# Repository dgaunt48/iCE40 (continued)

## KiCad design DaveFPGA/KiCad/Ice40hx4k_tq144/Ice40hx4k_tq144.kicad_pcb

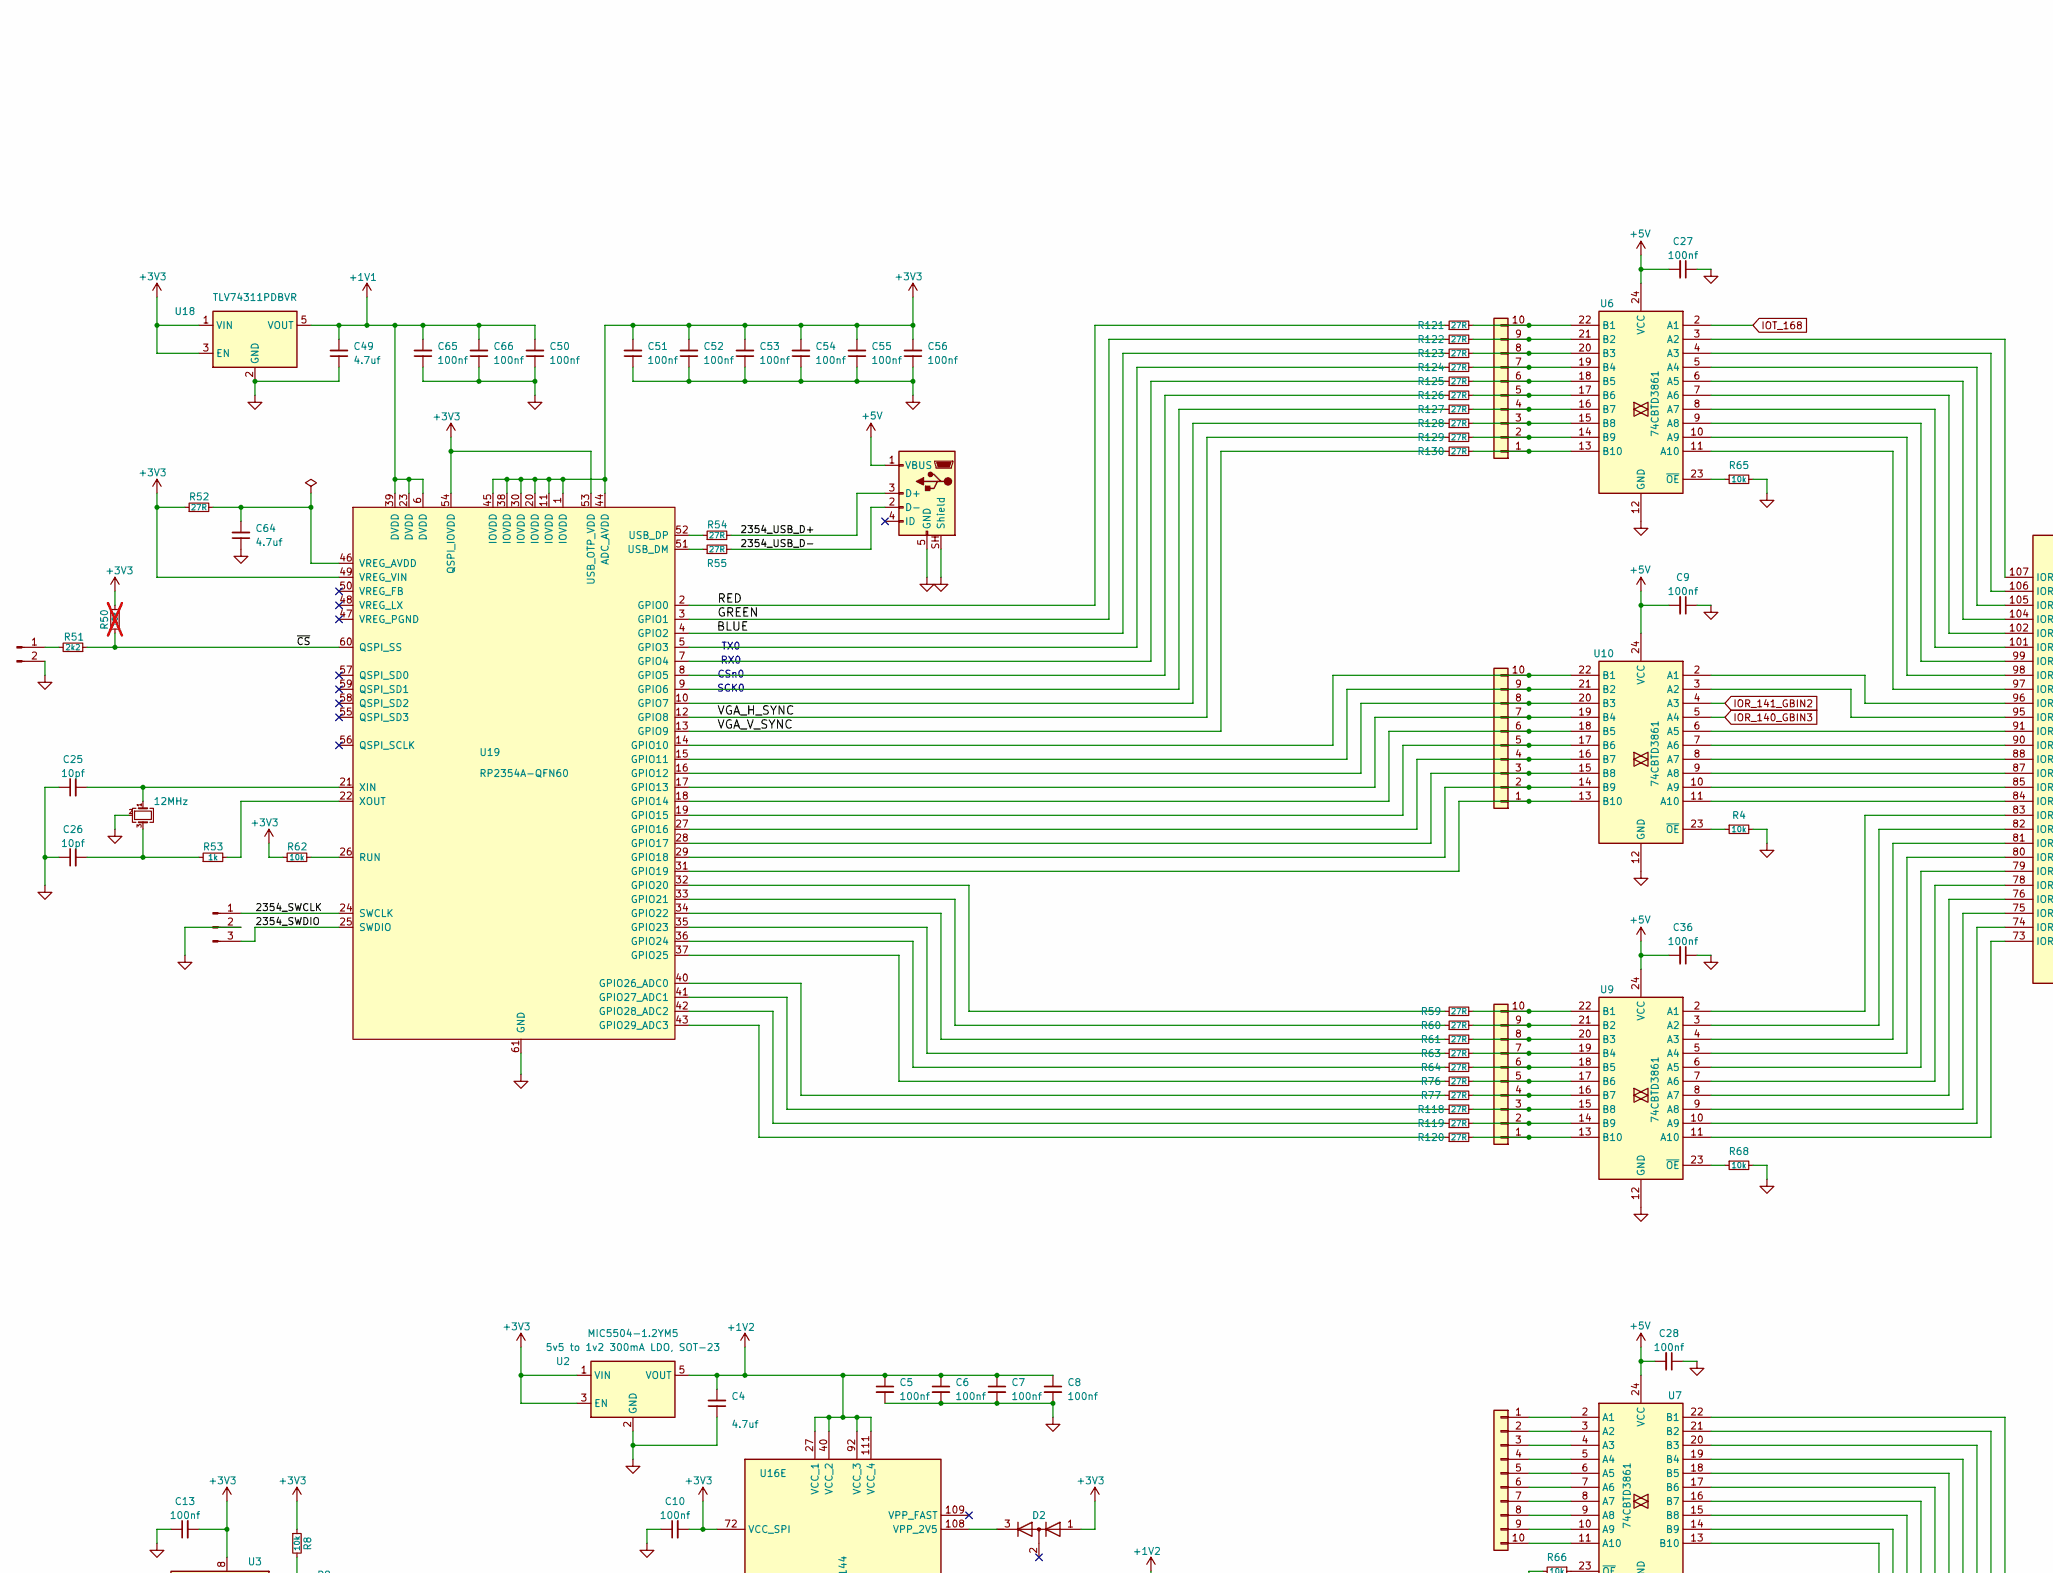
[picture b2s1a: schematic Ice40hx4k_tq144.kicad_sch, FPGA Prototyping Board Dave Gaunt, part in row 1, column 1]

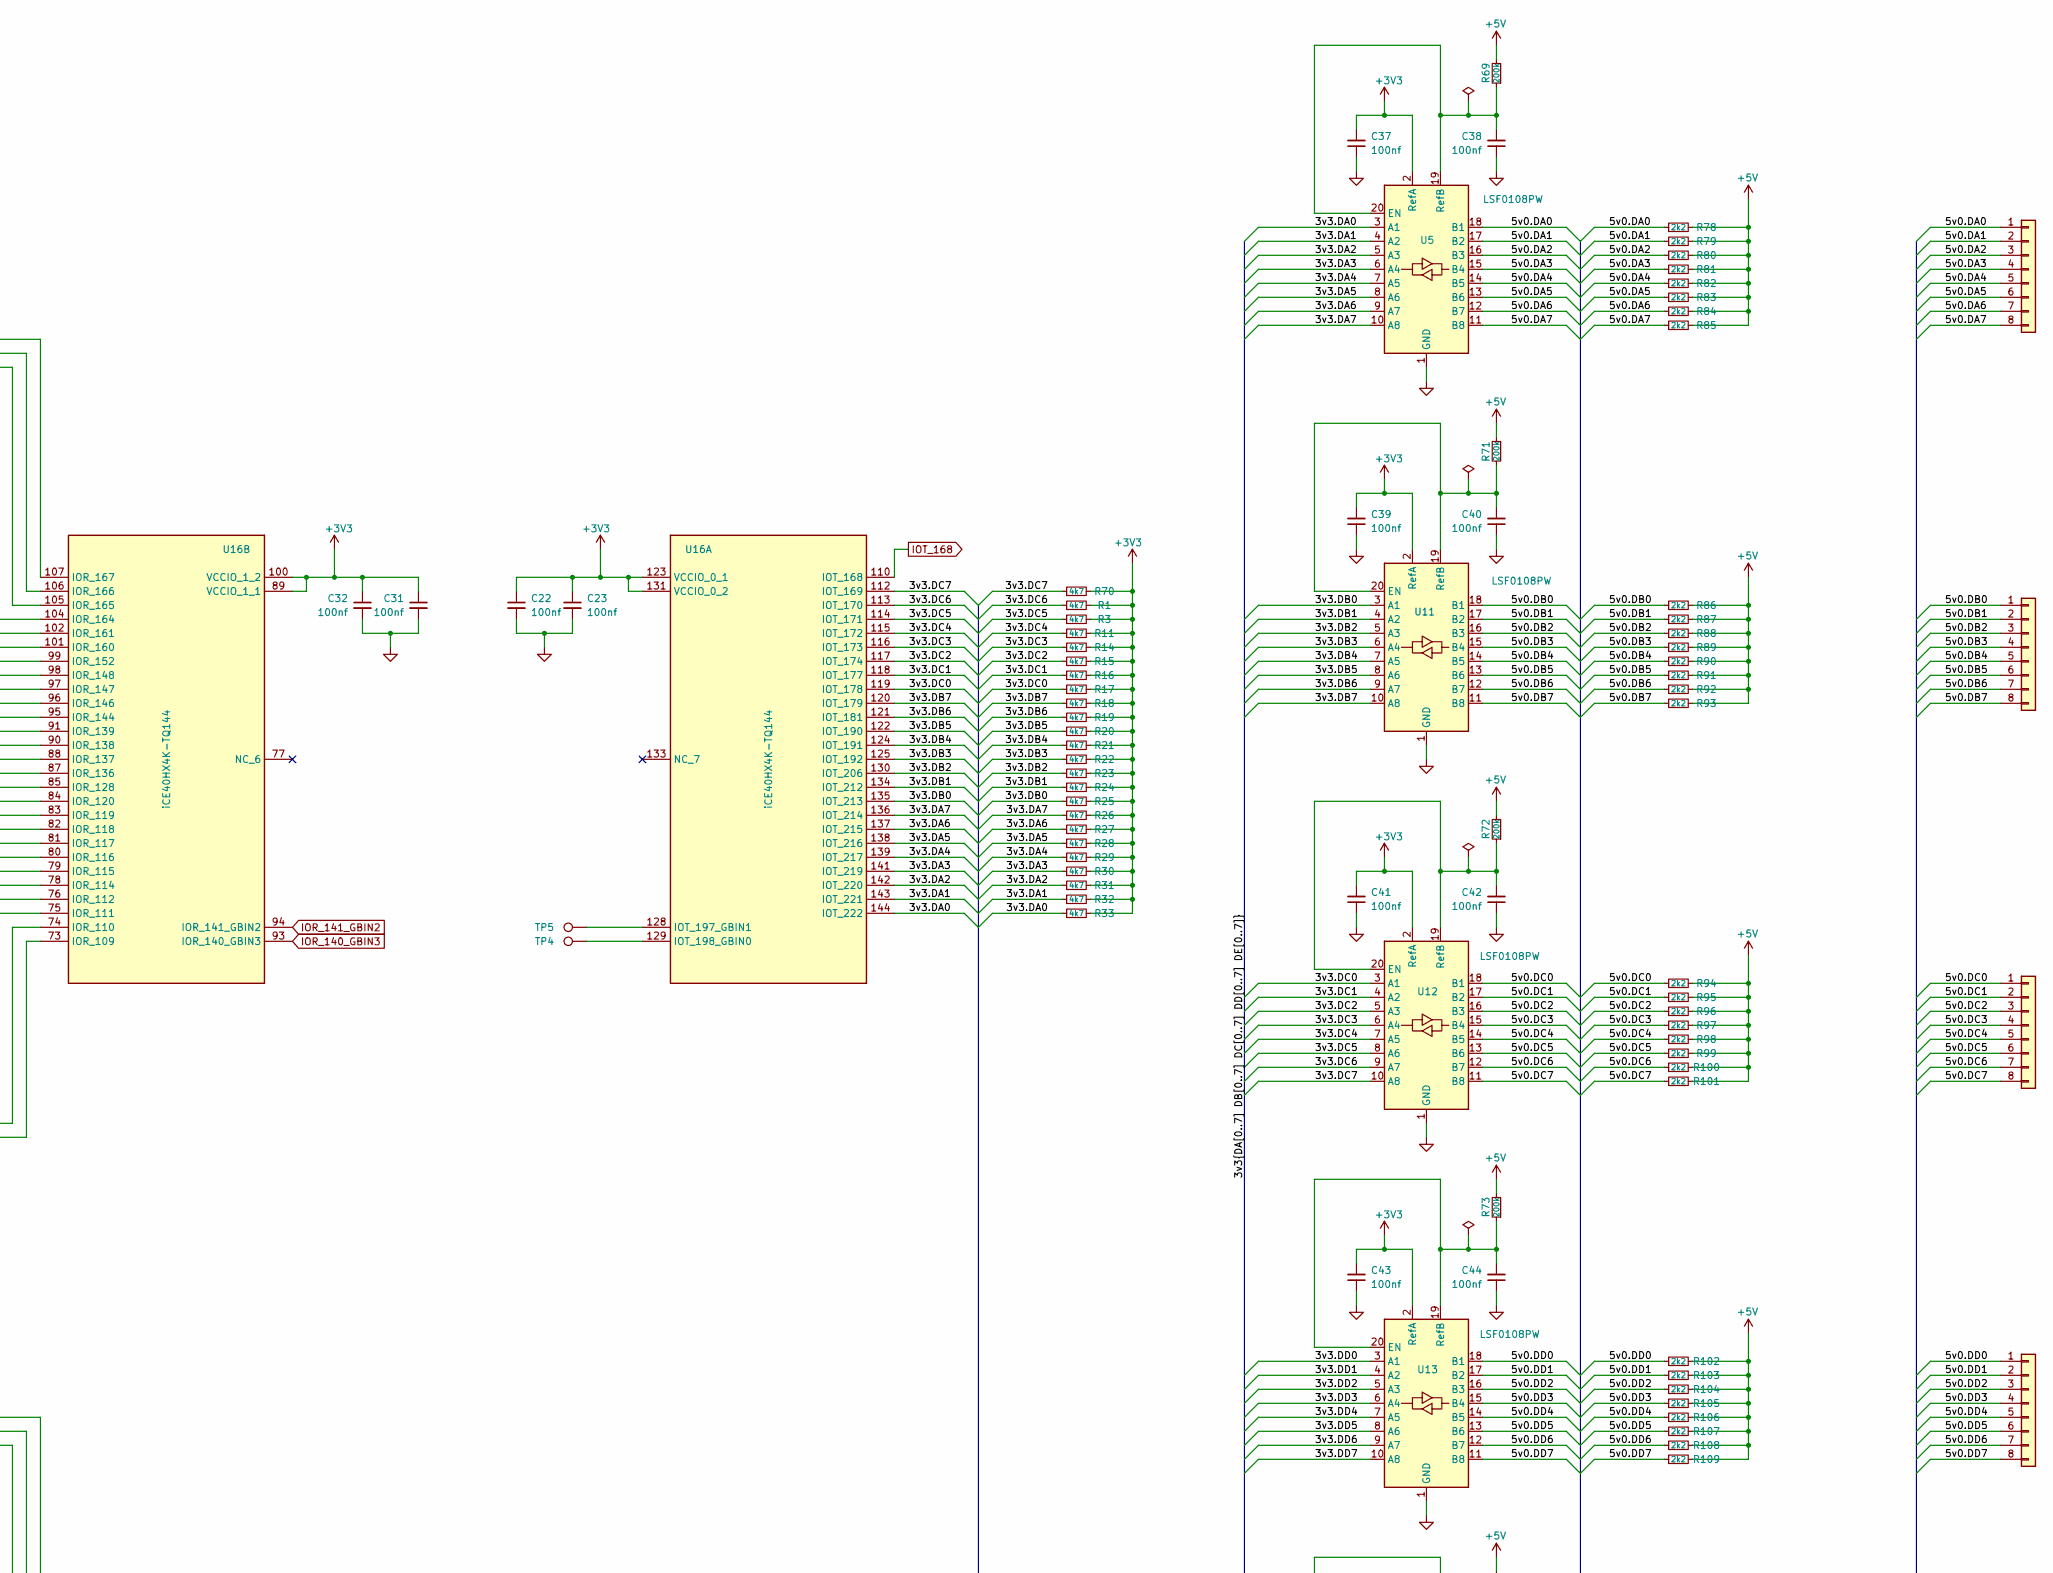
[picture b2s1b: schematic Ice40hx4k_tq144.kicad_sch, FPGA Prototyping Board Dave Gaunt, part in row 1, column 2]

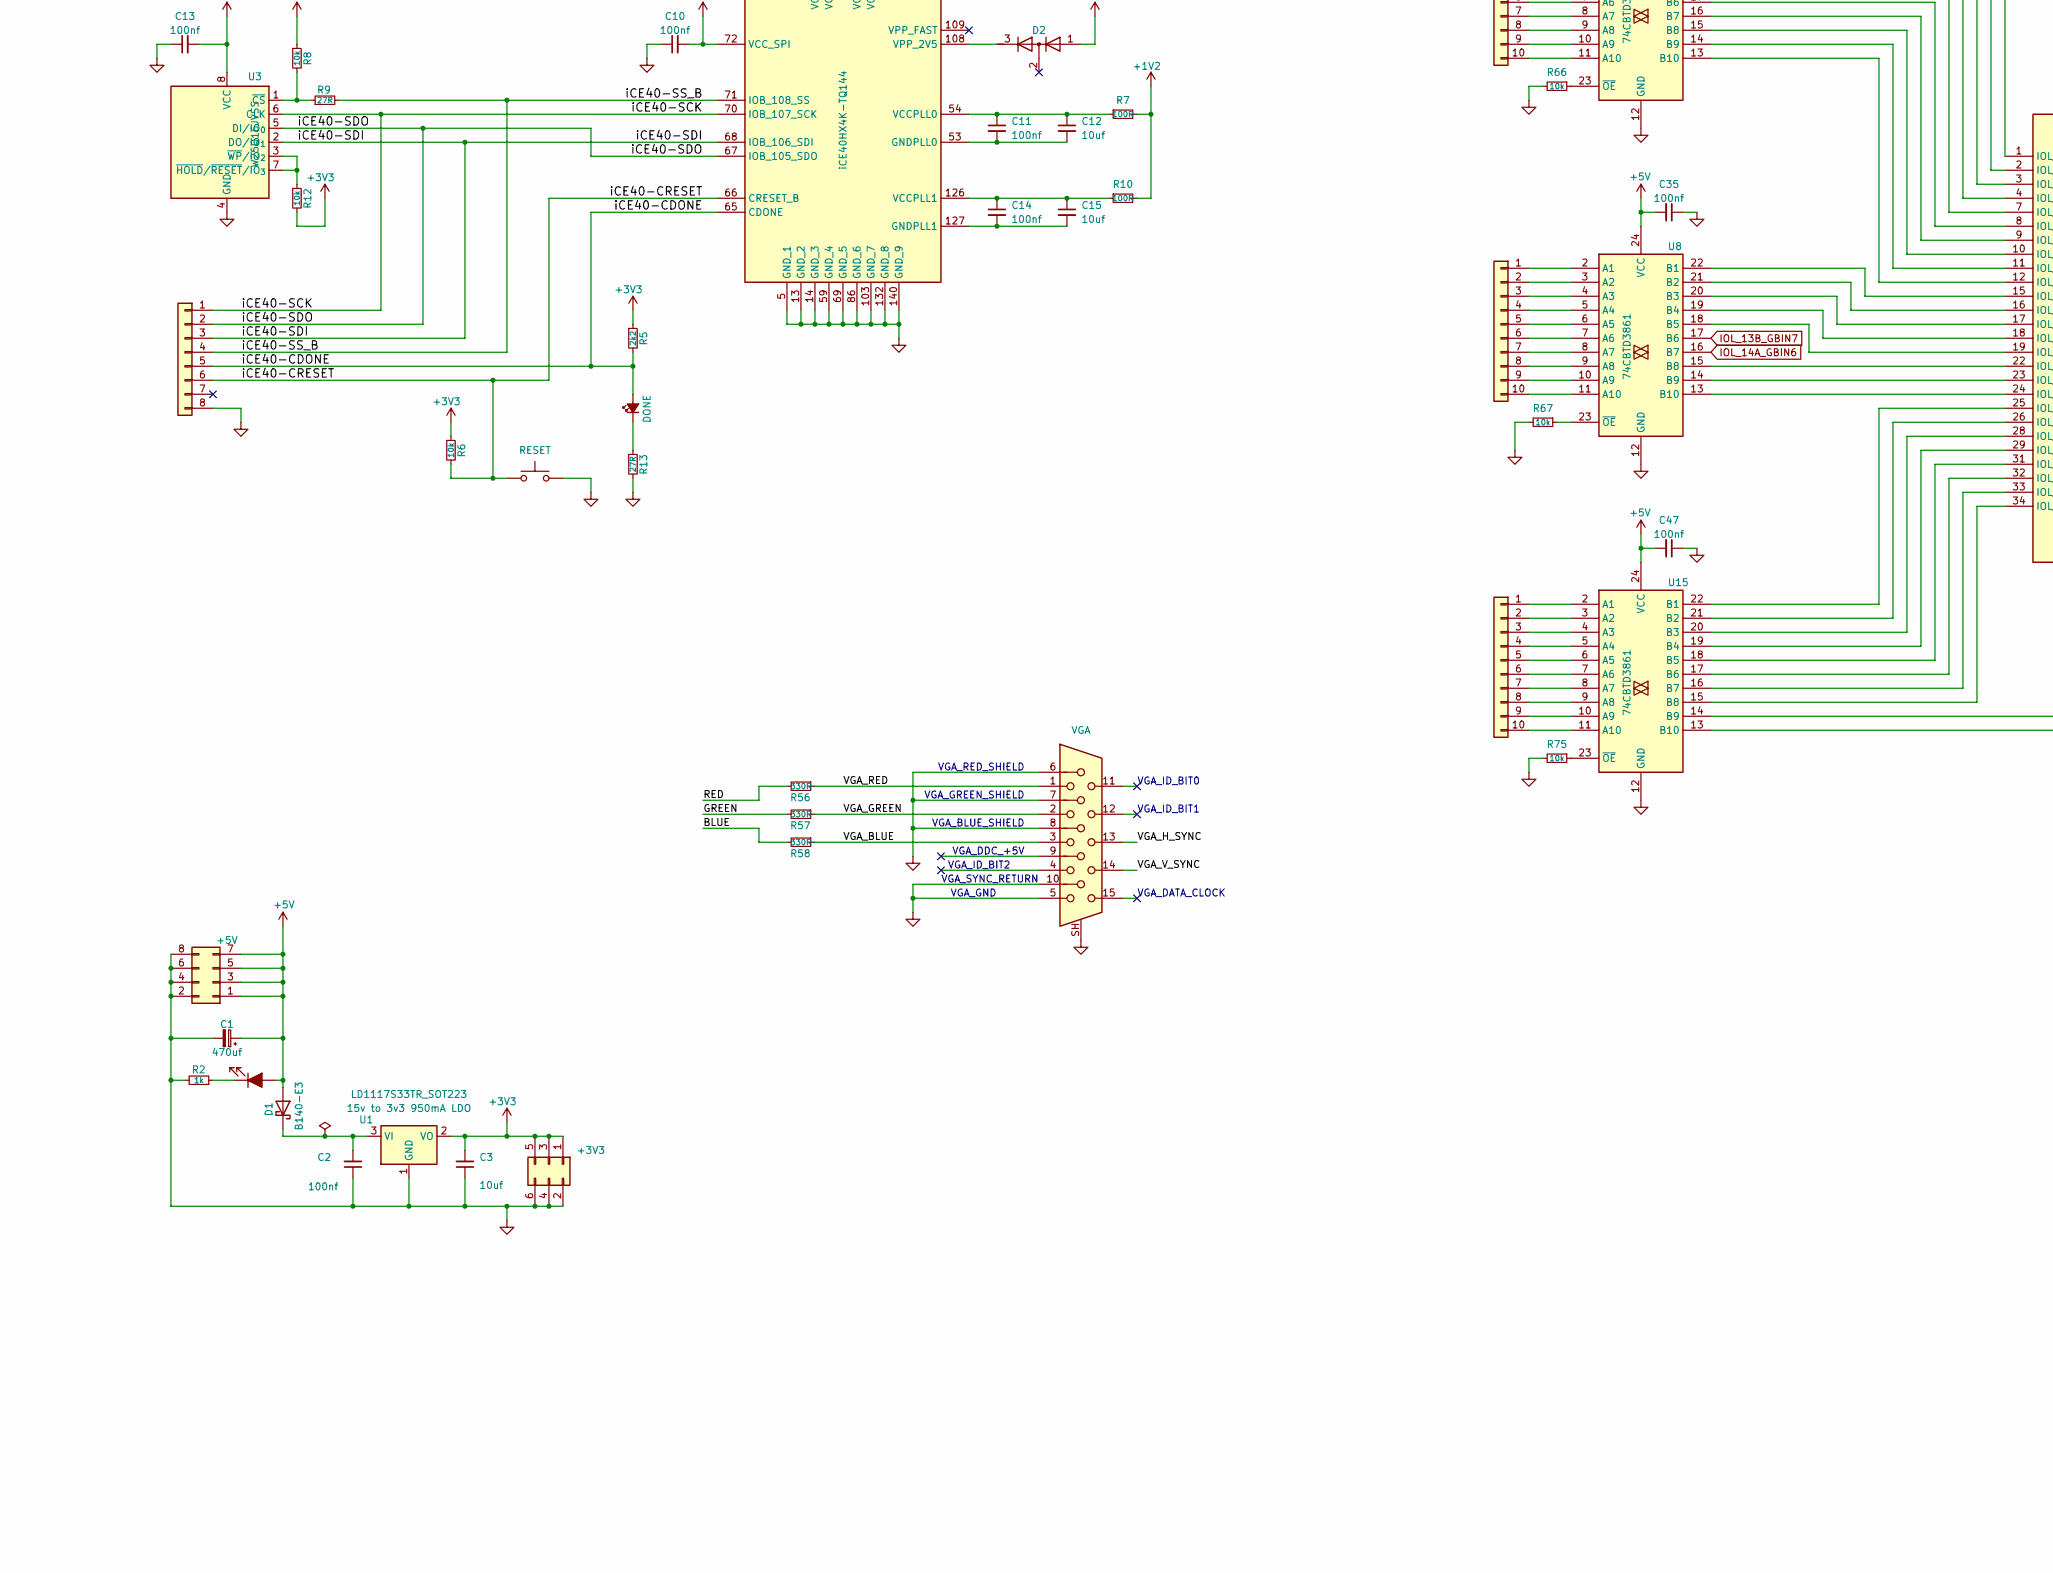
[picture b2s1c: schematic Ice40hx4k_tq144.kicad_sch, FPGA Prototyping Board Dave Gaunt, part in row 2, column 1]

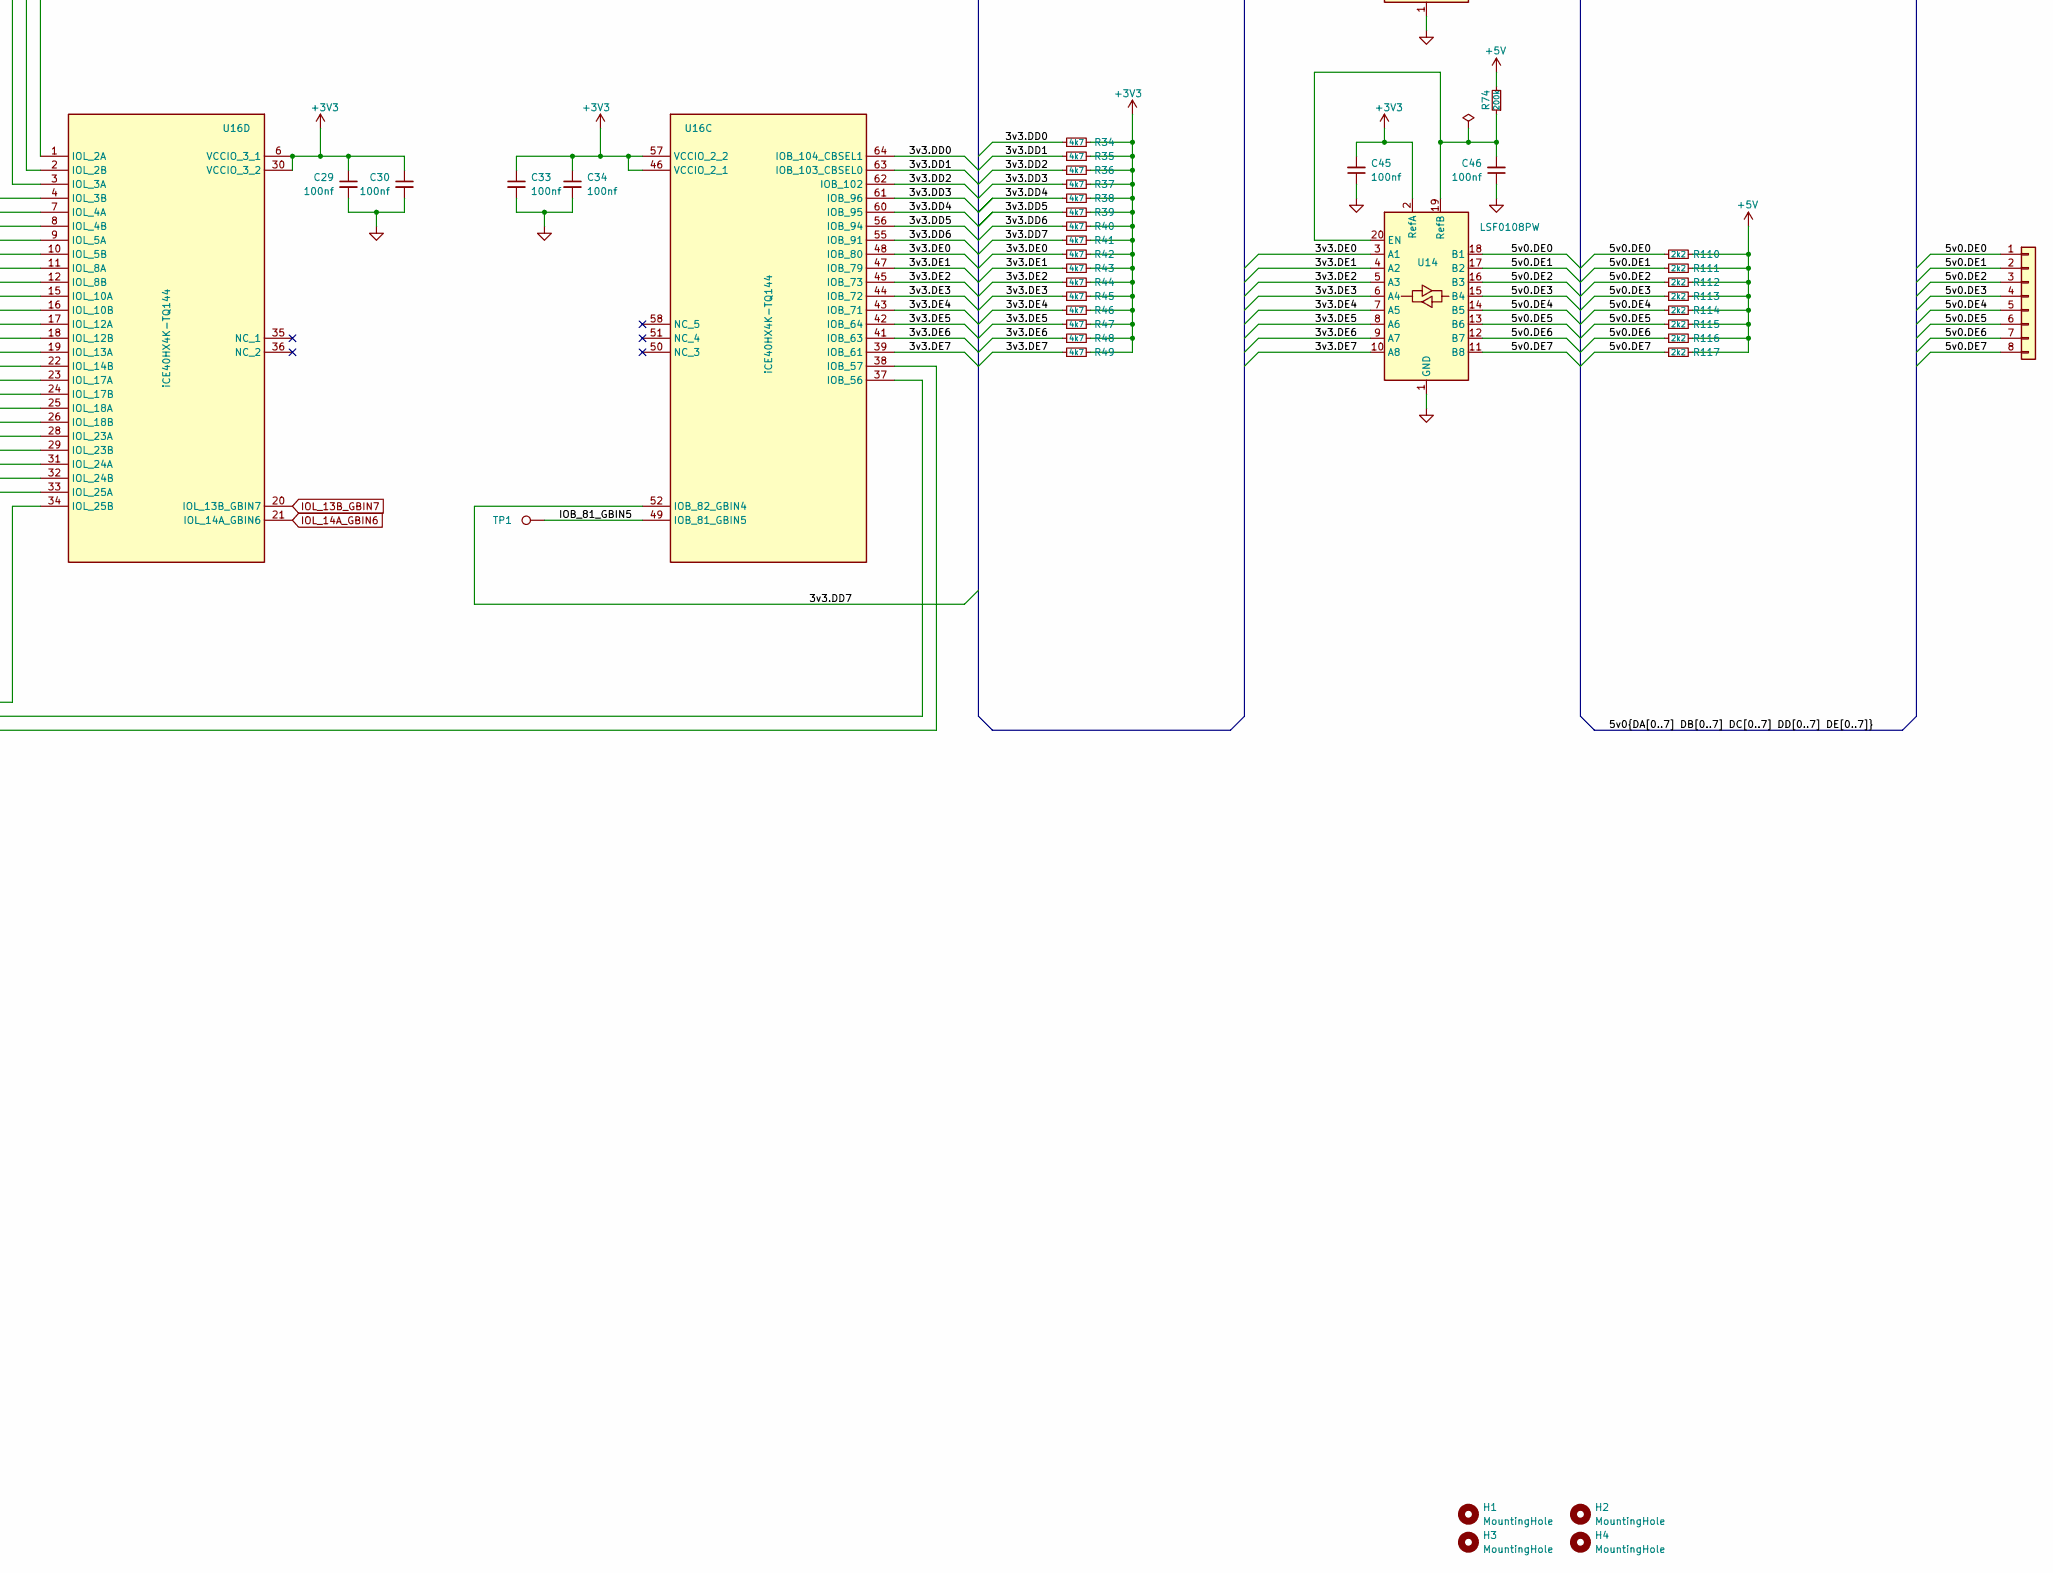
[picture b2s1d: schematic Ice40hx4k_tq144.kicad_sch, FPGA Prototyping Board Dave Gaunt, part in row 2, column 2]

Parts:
C1: 470uf; CP_Radial_D5.0mm_P2.50mm
C2, C5, C6, C7, C8, C9, C10, C11, C13, C14, C22, C23, C27, C28, C29, C30, C31, C32, C33, C34, C35, C36, C37, C38, C39, C40, C41, C42, C43, C44, C45, C46, C47, C50, C51, C52, C53, C54, C55, C56, C65, C66: 100nf; C_0603_1608Metric
C3, C12, C15: 10uf; C_0805_2012Metric
C4, C49, C64: 4.7uf; C_0603_1608Metric
C25, C26: 10pf; C_0603_1608Metric
CDone1: DONE; LED_0805_2012Metric
D1: B140-E3; D_SOD-123
D2: D_Dual_Series_ACK; SOT-23
H1, H2, H3, H4: MountingHole; MountingHole_3.5mm
J1: +5V; PinHeader_2x04_P2.54mm_Vertical
J2: +3V3; PinHeader_2x03_P2.54mm_Vertical
J3: SWD; PinHeader_1x03_P2.54mm_Vertical
J4: VGA; DSUB-15
J9: 2354 BOOT SEL; PinHeader_1x02_P2.54mm_Vertical
J10, J11, J13, J14, J15, J20: PinHeader_2x05_P2.54mm_Vertical
J12, J16, J17, J18, J19: PinHeader_2x04_P2.54mm_Vertical
J21: PROGRAM; PinHeader_1x08_P2.54mm_Vertical
J22: USB_B_Micro; USB_Micro-B_Amphenol_10103594-0001LF_Horizontal
Power1: POWER; LED_0805_2012Metric
R1, R3, R11, R14, R15, R16, R17, R18, R19, R20, R21, R22, R23, R24, R25, R26, R27, R28, R29, R30, R31, R32, R33, R34, R35, R36, R37, R38, R39, R40, R41, R42, R43, R44, R45, R46, R47, R48, R49, R70: 4k7; R_0603_1608Metric
R2, R53: 1k; R_0603_1608Metric
R4, R6, R8, R12, R62, R65, R66, R67, R68, R75: 10k; R_0603_1608Metric
R5, R51, R78, R79, R80, R81, R82, R83, R84, R85, R86, R87, R88, R89, R90, R91, R92, R93, R94, R95, R96, R97, R98, R99, R100, R101, R102, R103, R104, R105, R106, R107, R108, R109, R110, R111, R112, R113, R114, R115, R116, R117: 2k2; R_0603_1608Metric
R7, R10: 100R; R_0603_1608Metric
R9, R13, R52, R54, R55, R59, R60, R61, R63, R64, R76, R77, R118, R119, R120, R121, R122, R123, R124, R125, R126, R127, R128, R129, R130: 27R; R_0603_1608Metric
R50: 10k; R_0603_1608Metric; not fitted
R56, R57, R58: 330R; R_0603_1608Metric
R69, R71, R72, R73, R74: 200k; R_0603_1608Metric
S1: RESET; SW_PUSH_6mm_H4.3mm; Mouser Part Number 653-B3F-1052-G
TP1, TP4, TP5: TestPoint; TestPoint_Pad_D1.0mm
U1: LD1117S33TR_SOT223; SOT-223-3_TabPin2; Voltage 3v3
U2: MIC5504-1.2YM5; SOT-23-5; Voltage 1v2
U3: W25Q16JVSS; SOIC-8_5.3x5.3mm_P1.27mm
U5, U11, U12, U13, U14: LSF0108PW; TSSOP-20_4.4x6.5mm_P0.65mm
U6, U7, U8, U9, U10, U15: 74CBTD3861; SSOP-24_3.9x8.7mm_P0.635mm
U16: iCE40HX4K-TQ144; LQFP-144_20x20mm_P0.5mm; Mouser Part Number 842-ICE40HX4K-TQ144
U18: TLV74311PDBVR; SOT-23-5; Voltage 1v1
U19: RP2354A-QFN60; RP2350A_QFN-60_EP_7.75x7.75_Pitch0.4mm
Y1: 12MHz; Crystal_SMD_SeikoEpson_FA238V-4Pin_3.2x2.5mm

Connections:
+1V1: C49.2, C50.2, C65.2, C66.2, U18.5 (VOUT), U19.6 (DVDD), U19.23 (DVDD), U19.39 (DVDD)
+1V2: C4.2, C5.1, C6.1, C7.1, C8.1, R7.2, R10.2, U2.5 (VOUT), U16.27 (VCC_1), U16.40 (VCC_2), U16.92 (VCC_3), U16.111 (VCC_4)
+3V3: C3.2, C10.2, C13.2, C22.1, C23.1, C29.1, C30.1, C31.1, C32.1, C33.1, C34.1, C37.2, C39.2, C41.2, C43.2, C45.2, C51.2, C52.2, C53.2, C54.2, C55.2, C56.2, D2.1 (A), J2.1, J2.3, J2.5, R1.2, R3.2, R5.1, R6.1, R8.1, R11.2, R12.2, R14.2, R15.2, R16.2, R17.2, R18.2, R19.2, R20.2, R21.2, R22.2, R23.2, R24.2, R25.2, R26.2, R27.2, R28.2, R29.2, R30.2, R31.2, R32.2, R33.2, R34.2, R35.2, R36.2, R37.2, R38.2, R39.2, R40.2, R41.2, R42.2, R43.2, R44.2, R45.2, R46.2, R47.2, R48.2, R49.2, R50.1, R52.1, R62.1, R70.2, U1.2 (VO), U2.1 (VIN), U2.3 (EN), U3.8 (VCC), U5.2 (RefA), U11.2 (RefA), U12.2 (RefA), U13.2 (RefA), U14.2 (RefA), U16.6 (VCCIO_3_1), U16.30 (VCCIO_3_2), U16.46 (VCCIO_2_1), U16.57 (VCCIO_2_2), U16.72 (VCC_SPI), U16.89 (VCCIO_1_1), U16.100 (VCCIO_1_2), U16.123 (VCCIO_0_1), U16.131 (VCCIO_0_2), U18.1 (VIN), U18.3 (EN), U19.1 (IOVDD), U19.11 (IOVDD), U19.20 (IOVDD), U19.30 (IOVDD), U19.38 (IOVDD), U19.44 (ADC_AVDD), U19.45 (IOVDD), U19.49 (VREG_VIN), U19.53 (USB_OTP_VDD), U19.54 (QSPI_IOVDD)
+5V: C1.1, C9.2, C27.2, C28.2, C35.2, C36.2, C47.2, D1.2 (A), J1.1, J1.3, J1.5, J1.7, J22.1 (VBUS), Power1.2 (A), R69.2, R71.1, R72.2, R73.2, R74.2, R78.2, R79.2, R80.2, R81.2, R82.2, R83.2, R84.2, R85.2, R86.2, R87.2, R88.2, R89.2, R90.2, R91.2, R92.2, R93.2, R94.2, R95.2, R96.2, R97.2, R98.2, R99.2, R100.2, R101.2, R102.2, R103.2, R104.2, R105.2, R106.2, R107.2, R108.2, R109.2, R110.2, R111.2, R112.2, R113.2, R114.2, R115.2, R116.2, R117.2, U6.24 (VCC), U7.24 (VCC), U8.24 (VCC), U9.24 (VCC), U10.24 (VCC), U15.24 (VCC)
/3v3.DA0: R33.1, U5.3 (A1), U16.144 (IOT_222)
/3v3.DA1: R32.1, U5.4 (A2), U16.143 (IOT_221)
/3v3.DA2: R31.1, U5.5 (A3), U16.142 (IOT_220)
/3v3.DA3: R30.1, U5.6 (A4), U16.141 (IOT_219)
/3v3.DA4: R29.1, U5.7 (A5), U16.139 (IOT_217)
/3v3.DA5: R28.1, U5.8 (A6), U16.138 (IOT_216)
/3v3.DA6: R27.1, U5.9 (A7), U16.137 (IOT_215)
/3v3.DA7: R26.1, U5.10 (A8), U16.136 (IOT_214)
/3v3.DB0: R25.1, U11.3 (A1), U16.135 (IOT_213)
/3v3.DB1: R24.1, U11.4 (A2), U16.134 (IOT_212)
/3v3.DB2: R23.1, U11.5 (A3), U16.130 (IOT_206)
/3v3.DB3: R22.1, U11.6 (A4), U16.125 (IOT_192)
/3v3.DB4: R21.1, U11.7 (A5), U16.124 (IOT_191)
/3v3.DB5: R20.1, U11.8 (A6), U16.122 (IOT_190)
/3v3.DB6: R19.1, U11.9 (A7), U16.121 (IOT_181)
/3v3.DB7: R18.1, U11.10 (A8), U16.120 (IOT_179)
/3v3.DC0: R17.1, U12.3 (A1), U16.119 (IOT_178)
/3v3.DC1: R16.1, U12.4 (A2), U16.118 (IOT_177)
/3v3.DC2: R15.1, U12.5 (A3), U16.117 (IOT_174)
/3v3.DC3: R14.1, U12.6 (A4), U16.116 (IOT_173)
/3v3.DC4: R11.1, U12.7 (A5), U16.115 (IOT_172)
/3v3.DC5: R3.1, U12.8 (A6), U16.114 (IOT_171)
/3v3.DC6: R1.1, U12.9 (A7), U16.113 (IOT_170)
/3v3.DC7: R70.1, U12.10 (A8), U16.112 (IOT_169)
/3v3.DD0: R34.1, U13.3 (A1), U16.64 (IOB_104_CBSEL1)
/3v3.DD1: R35.1, U13.4 (A2), U16.63 (IOB_103_CBSEL0)
/3v3.DD2: R36.1, U13.5 (A3), U16.62 (IOB_102)
/3v3.DD3: R37.1, U13.6 (A4), U16.61 (IOB_96)
/3v3.DD4: R38.1, U13.7 (A5), U16.60 (IOB_95)
/3v3.DD5: R39.1, U13.8 (A6), U16.56 (IOB_94)
/3v3.DD6: R40.1, U13.9 (A7), U16.55 (IOB_91)
/3v3.DD7: R41.1, U13.10 (A8), U16.52 (IOB_82_GBIN4)
/3v3.DE0: R42.1, U14.3 (A1), U16.48 (IOB_80)
/3v3.DE1: R43.1, U14.4 (A2), U16.47 (IOB_79)
/3v3.DE2: R44.1, U14.5 (A3), U16.45 (IOB_73)
/3v3.DE3: R45.1, U14.6 (A4), U16.44 (IOB_72)
/3v3.DE4: R46.1, U14.7 (A5), U16.43 (IOB_71)
/3v3.DE5: R47.1, U14.8 (A6), U16.42 (IOB_64)
/3v3.DE6: R48.1, U14.9 (A7), U16.41 (IOB_63)
/3v3.DE7: R49.1, U14.10 (A8), U16.39 (IOB_61)
/5v0.DA0: J19.1, R78.1, U5.18 (B1)
/5v0.DA1: J19.2, R79.1, U5.17 (B2)
/5v0.DA2: J19.3, R80.1, U5.16 (B3)
/5v0.DA3: J19.4, R81.1, U5.15 (B4)
/5v0.DA4: J19.5, R82.1, U5.14 (B5)
/5v0.DA5: J19.6, R83.1, U5.13 (B6)
/5v0.DA6: J19.7, R84.1, U5.12 (B7)
/5v0.DA7: J19.8, R85.1, U5.11 (B8)
/5v0.DB0: J18.1, R86.1, U11.18 (B1)
/5v0.DB1: J18.2, R87.1, U11.17 (B2)
/5v0.DB2: J18.3, R88.1, U11.16 (B3)
/5v0.DB3: J18.4, R89.1, U11.15 (B4)
/5v0.DB4: J18.5, R90.1, U11.14 (B5)
/5v0.DB5: J18.6, R91.1, U11.13 (B6)
/5v0.DB6: J18.7, R92.1, U11.12 (B7)
/5v0.DB7: J18.8, R93.1, U11.11 (B8)
/5v0.DC0: J17.1, R94.1, U12.18 (B1)
/5v0.DC1: J17.2, R95.1, U12.17 (B2)
/5v0.DC2: J17.3, R96.1, U12.16 (B3)
/5v0.DC3: J17.4, R97.1, U12.15 (B4)
/5v0.DC4: J17.5, R98.1, U12.14 (B5)
/5v0.DC5: J17.6, R99.1, U12.13 (B6)
/5v0.DC6: J17.7, R100.1, U12.12 (B7)
/5v0.DC7: J17.8, R101.1, U12.11 (B8)
/5v0.DD0: J16.1, R102.1, U13.18 (B1)
/5v0.DD1: J16.2, R103.1, U13.17 (B2)
/5v0.DD2: J16.3, R104.1, U13.16 (B3)
/5v0.DD3: J16.4, R105.1, U13.15 (B4)
/5v0.DD4: J16.5, R106.1, U13.14 (B5)
/5v0.DD5: J16.6, R107.1, U13.13 (B6)
/5v0.DD6: J16.7, R108.1, U13.12 (B7)
/5v0.DD7: J16.8, R109.1, U13.11 (B8)
/5v0.DE0: J12.1, R110.1, U14.18 (B1)
/5v0.DE1: J12.2, R111.1, U14.17 (B2)
/5v0.DE2: J12.3, R112.1, U14.16 (B3)
/5v0.DE3: J12.4, R113.1, U14.15 (B4)
/5v0.DE4: J12.5, R114.1, U14.14 (B5)
/5v0.DE5: J12.6, R115.1, U14.13 (B6)
/5v0.DE6: J12.7, R116.1, U14.12 (B7)
/5v0.DE7: J12.8, R117.1, U14.11 (B8)
/2354_SWCLK: J3.1, U19.24 (SWCLK)
/2354_SWDIO: J3.3, U19.25 (SWDIO)
/2354_USB_D+: J22.3 (D+), R54.2
/2354_USB_D-: J22.2 (D-), R55.2
/BLUE: R58.2, R123.1, U19.4 (GPIO2)
/GREEN: R57.2, R122.1, U19.3 (GPIO1)
/IOB_81_GBIN5: TP1.1 (1_1), U16.49 (IOB_81_GBIN5)
/RED: R56.2, R121.1, U19.2 (GPIO0)
/VGA_BLUE: J4.3, R58.1
/VGA_GREEN: J4.2, R57.1
/VGA_H_SYNC: J4.13, R129.1, U19.12 (GPIO8)
/VGA_RED: J4.1, R56.1
/VGA_V_SYNC: J4.14, R130.1, U19.13 (GPIO9)
/iCE40-CDONE: CDone1.2 (A), J21.5, R5.2, U16.65 (CDONE)
/iCE40-CRESET: J21.6, R6.2, S1.1, U16.66 (CRESET_B)
/iCE40-SCK: J21.1, U3.6 (CLK), U16.70 (IOB_107_SCK)
/iCE40-SDI: J21.3, U3.2 (DO/IO_{1}), U16.68 (IOB_106_SDI)
/iCE40-SDO: J21.2, U3.5 (DI/IO_{0}), U16.67 (IOB_105_SDO)
/iCE40-SS_B: J21.4, R9.2, U16.71 (IOB_108_SS)
/~CS: R50.2, R51.1, U19.60 (QSPI_SS)
GND: C1.2, C2.1, C3.1, C4.1, C5.2, C6.2, C7.2, C8.2, C9.1, C10.1, C13.1, C22.2, C23.2, C25.1, C26.1, C27.1, C28.1, C29.2, C30.2, C31.2, C32.2, C33.2, C34.2, C35.1, C36.1, C37.1, C38.1, C39.1, C40.1, C41.1, C42.1, C43.1, C44.1, C45.1, C46.1, C47.1, C49.1, C50.1, C51.1, C52.1, C53.1, C54.1, C55.1, C56.1, C64.1, C65.1, C66.1, J1.2, J1.4, J1.6, J1.8, J2.2, J2.4, J2.6, J3.2, J4.5, J4.6, J4.7, J4.8, J4.10, J4.SH, J9.2, J21.8, J22.5 (GND), J22.SH (Shield), R2.2, R4.2, R13.2, R65.2, R66.2, R67.2, R68.2, R75.2, S1.2, U1.1 (GND), U2.2 (GND), U3.4 (GND), U5.1 (GND), U6.12 (GND), U7.12 (GND), U8.12 (GND), U9.12 (GND), U10.12 (GND), U11.1 (GND), U12.1 (GND), U13.1 (GND), U14.1 (GND), U15.12 (GND), U16.5 (GND_1), U16.13 (GND_2), U16.14 (GND_3), U16.59 (GND_4), U16.69 (GND_5), U16.86 (GND_6), U16.103 (GND_7), U16.132 (GND_8), U16.140 (GND_9), U18.2 (GND), U19.61 (GND), Y1.2 (G), Y1.4 (G)
IOL_13B_GBIN7: U8.17 (B6), U16.20 (IOL_13B_GBIN7)
IOL_14A_GBIN6: U8.16 (B7), U16.21 (IOL_14A_GBIN6)
IOR_140_GBIN3: U10.5 (A4), U16.93 (IOR_140_GBIN3)
IOR_141_GBIN2: U10.4 (A3), U16.94 (IOR_141_GBIN2)
IOT_168: U6.2 (A1), U16.110 (IOT_168)
unnamed: C26.2, R53.1, Y1.3
unnamed: CDone1.1 (K), R13.1
unnamed: C2.2, D1.1 (K), U1.3 (VI)
unnamed: D2.3 (K), U16.108 (VPP_2V5)
unnamed: J9.1, R51.2
unnamed: J10.1, R120.2, U9.13 (B10)
unnamed: J10.2, R119.2, U9.14 (B9)
unnamed: J10.3, R118.2, U9.15 (B8)
unnamed: J10.4, R77.2, U9.16 (B7)
unnamed: J10.5, R76.2, U9.17 (B6)
unnamed: J10.6, R64.2, U9.18 (B5)
unnamed: J10.7, R63.2, U9.19 (B4)
unnamed: J10.8, R61.2, U9.20 (B3)
unnamed: J10.9, R60.2, U9.21 (B2)
unnamed: J10.10, R59.2, U9.22 (B1)
unnamed: J11.1, U10.13 (B10), U19.31 (GPIO19)
unnamed: J11.2, U10.14 (B9), U19.29 (GPIO18)
unnamed: J11.3, U10.15 (B8), U19.28 (GPIO17)
unnamed: J11.4, U10.16 (B7), U19.27 (GPIO16)
unnamed: J11.5, U10.17 (B6), U19.19 (GPIO15)
unnamed: J11.6, U10.18 (B5), U19.18 (GPIO14)
unnamed: J11.7, U10.19 (B4), U19.17 (GPIO13)
unnamed: J11.8, U10.20 (B3), U19.16 (GPIO12)
unnamed: J11.9, U10.21 (B2), U19.15 (GPIO11)
unnamed: J11.10, U10.22 (B1), U19.14 (GPIO10)
unnamed: J13.1, R130.2, U6.13 (B10)
unnamed: J13.2, R129.2, U6.14 (B9)
unnamed: J13.3, R128.2, U6.15 (B8)
unnamed: J13.4, R127.2, U6.16 (B7)
unnamed: J13.5, R126.2, U6.17 (B6)
unnamed: J13.6, R125.2, U6.18 (B5)
unnamed: J13.7, R124.2, U6.19 (B4)
unnamed: J13.8, R123.2, U6.20 (B3)
unnamed: J13.9, R122.2, U6.21 (B2)
unnamed: J13.10, R121.2, U6.22 (B1)
unnamed: J14.1, U7.2 (A1)
unnamed: J14.2, U7.3 (A2)
unnamed: J14.3, U7.4 (A3)
unnamed: J14.4, U7.5 (A4)
unnamed: J14.5, U7.6 (A5)
unnamed: J14.6, U7.7 (A6)
unnamed: J14.7, U7.8 (A7)
unnamed: J14.8, U7.9 (A8)
unnamed: J14.9, U7.10 (A9)
unnamed: J14.10, U7.11 (A10)
unnamed: J15.1, U8.2 (A1)
unnamed: J15.2, U8.3 (A2)
unnamed: J15.3, U8.4 (A3)
unnamed: J15.4, U8.5 (A4)
unnamed: J15.5, U8.6 (A5)
unnamed: J15.6, U8.7 (A6)
unnamed: J15.7, U8.8 (A7)
unnamed: J15.8, U8.9 (A8)
unnamed: J15.9, U8.10 (A9)
unnamed: J15.10, U8.11 (A10)
unnamed: J20.1, U15.2 (A1)
unnamed: J20.2, U15.3 (A2)
unnamed: J20.3, U15.4 (A3)
unnamed: J20.4, U15.5 (A4)
unnamed: J20.5, U15.6 (A5)
unnamed: J20.6, U15.7 (A6)
unnamed: J20.7, U15.8 (A7)
unnamed: J20.8, U15.9 (A8)
unnamed: J20.9, U15.10 (A9)
unnamed: J20.10, U15.11 (A10)
unnamed: Power1.1 (K), R2.1
unnamed: R8.2, R9.1, U3.1 (~CS)
unnamed: R12.1, U3.3 (~WP/IO_{2}), U3.7 (~HOLD/~RESET/IO_{3})
unnamed: C38.2, R69.1, U5.19 (RefB), U5.20 (EN)
unnamed: R65.1, U6.23 (~OE)
unnamed: R66.1, U7.23 (~OE)
unnamed: R67.1, U8.23 (~OE)
unnamed: R68.1, U9.23 (~OE)
unnamed: U10.2 (A1), U16.96 (IOR_146)
unnamed: U10.3 (A2), U16.95 (IOR_144)
unnamed: U10.6 (A5), U16.91 (IOR_139)
unnamed: U10.7 (A6), U16.90 (IOR_138)
unnamed: U10.8 (A7), U16.88 (IOR_137)
unnamed: U10.9 (A8), U16.87 (IOR_136)
unnamed: U10.10 (A9), U16.85 (IOR_128)
unnamed: U10.11 (A10), U16.84 (IOR_120)
unnamed: R4.1, U10.23 (~OE)
unnamed: C40.2, R71.2, U11.19 (RefB), U11.20 (EN)
unnamed: C42.2, R72.1, U12.19 (RefB), U12.20 (EN)
unnamed: C44.2, R73.1, U13.19 (RefB), U13.20 (EN)
unnamed: C46.2, R74.1, U14.19 (RefB), U14.20 (EN)
unnamed: U15.22 (B1), U16.25 (IOL_18A)
unnamed: U15.21 (B2), U16.26 (IOL_18B)
unnamed: U15.20 (B3), U16.28 (IOL_23A)
unnamed: U15.19 (B4), U16.29 (IOL_23B)
unnamed: U15.18 (B5), U16.31 (IOL_24A)
unnamed: U15.17 (B6), U16.32 (IOL_24B)
unnamed: U15.16 (B7), U16.33 (IOL_25A)
unnamed: U15.15 (B8), U16.34 (IOL_25B)
unnamed: U15.14 (B9), U16.37 (IOB_56)
unnamed: U15.13 (B10), U16.38 (IOB_57)
unnamed: R75.1, U15.23 (~OE)
unnamed: TP5.1 (1_1), U16.128 (IOT_197_GBIN1)
unnamed: TP4.1 (1_1), U16.129 (IOT_198_GBIN0)
unnamed: U9.11 (A10), U16.73 (IOR_109)
unnamed: U9.10 (A9), U16.74 (IOR_110)
unnamed: U9.9 (A8), U16.75 (IOR_111)
unnamed: U9.8 (A7), U16.76 (IOR_112)
unnamed: U9.7 (A6), U16.78 (IOR_114)
unnamed: U9.6 (A5), U16.79 (IOR_115)
unnamed: U9.5 (A4), U16.80 (IOR_116)
unnamed: U9.4 (A3), U16.81 (IOR_117)
unnamed: U9.3 (A2), U16.82 (IOR_118)
unnamed: U9.2 (A1), U16.83 (IOR_119)
unnamed: U6.11 (A10), U16.97 (IOR_147)
unnamed: U6.10 (A9), U16.98 (IOR_148)
unnamed: U6.9 (A8), U16.99 (IOR_152)
unnamed: U6.8 (A7), U16.101 (IOR_160)
unnamed: U6.7 (A6), U16.102 (IOR_161)
unnamed: U6.6 (A5), U16.104 (IOR_164)
unnamed: U6.5 (A4), U16.105 (IOR_165)
unnamed: U6.4 (A3), U16.106 (IOR_166)
unnamed: U6.3 (A2), U16.107 (IOR_167)
unnamed: U7.22 (B1), U16.1 (IOL_2A)
unnamed: U7.21 (B2), U16.2 (IOL_2B)
unnamed: U7.20 (B3), U16.3 (IOL_3A)
unnamed: U7.19 (B4), U16.4 (IOL_3B)
unnamed: U7.18 (B5), U16.7 (IOL_4A)
unnamed: U7.17 (B6), U16.8 (IOL_4B)
unnamed: U7.16 (B7), U16.9 (IOL_5A)
unnamed: U7.15 (B8), U16.10 (IOL_5B)
unnamed: U7.14 (B9), U16.11 (IOL_8A)
unnamed: U7.13 (B10), U16.12 (IOL_8B)
unnamed: U8.22 (B1), U16.15 (IOL_10A)
unnamed: U8.21 (B2), U16.16 (IOL_10B)
unnamed: U8.20 (B3), U16.17 (IOL_12A)
unnamed: U8.19 (B4), U16.18 (IOL_12B)
unnamed: U8.18 (B5), U16.19 (IOL_13A)
unnamed: U8.15 (B8), U16.22 (IOL_14B)
unnamed: U8.14 (B9), U16.23 (IOL_17A)
unnamed: U8.13 (B10), U16.24 (IOL_17B)
unnamed: C11.2, C12.2, U16.53 (GNDPLL0)
unnamed: C14.2, C15.2, U16.127 (GNDPLL1)
unnamed: C11.1, C12.1, R7.1, U16.54 (VCCPLL0)
unnamed: C14.1, C15.1, R10.1, U16.126 (VCCPLL1)
unnamed: R124.1, U19.5 (GPIO3)
unnamed: R125.1, U19.7 (GPIO4)
unnamed: R126.1, U19.8 (GPIO5)
unnamed: R127.1, U19.9 (GPIO6)
unnamed: R128.1, U19.10 (GPIO7)
unnamed: R59.1, U19.32 (GPIO20)
unnamed: R60.1, U19.33 (GPIO21)
unnamed: R61.1, U19.34 (GPIO22)
unnamed: R63.1, U19.35 (GPIO23)
unnamed: R64.1, U19.36 (GPIO24)
unnamed: R76.1, U19.37 (GPIO25)
unnamed: R77.1, U19.40 (GPIO26_ADC0)
unnamed: R118.1, U19.41 (GPIO27_ADC1)
unnamed: R119.1, U19.42 (GPIO28_ADC2)
unnamed: R120.1, U19.43 (GPIO29_ADC3)
unnamed: R62.2, U19.26 (RUN)
unnamed: R55.1, U19.51 (USB_DM)
unnamed: R54.1, U19.52 (USB_DP)
unnamed: C64.2, R52.2, U19.46 (VREG_AVDD)
unnamed: C25.2, U19.21 (XIN), Y1.1
unnamed: R53.2, U19.22 (XOUT)

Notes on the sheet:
VGA_GREEN_SHIELD
VGA_GND
VGA_DDC_+5V
RX0
SCK0
VGA_SYNC_RETURN
VGA_DATA_CLOCK
VGA_ID_BIT1
TX0
VGA_RED_SHIELD
CSn0
VGA_ID_BIT0
VGA_BLUE_SHIELD
VGA_ID_BIT2
